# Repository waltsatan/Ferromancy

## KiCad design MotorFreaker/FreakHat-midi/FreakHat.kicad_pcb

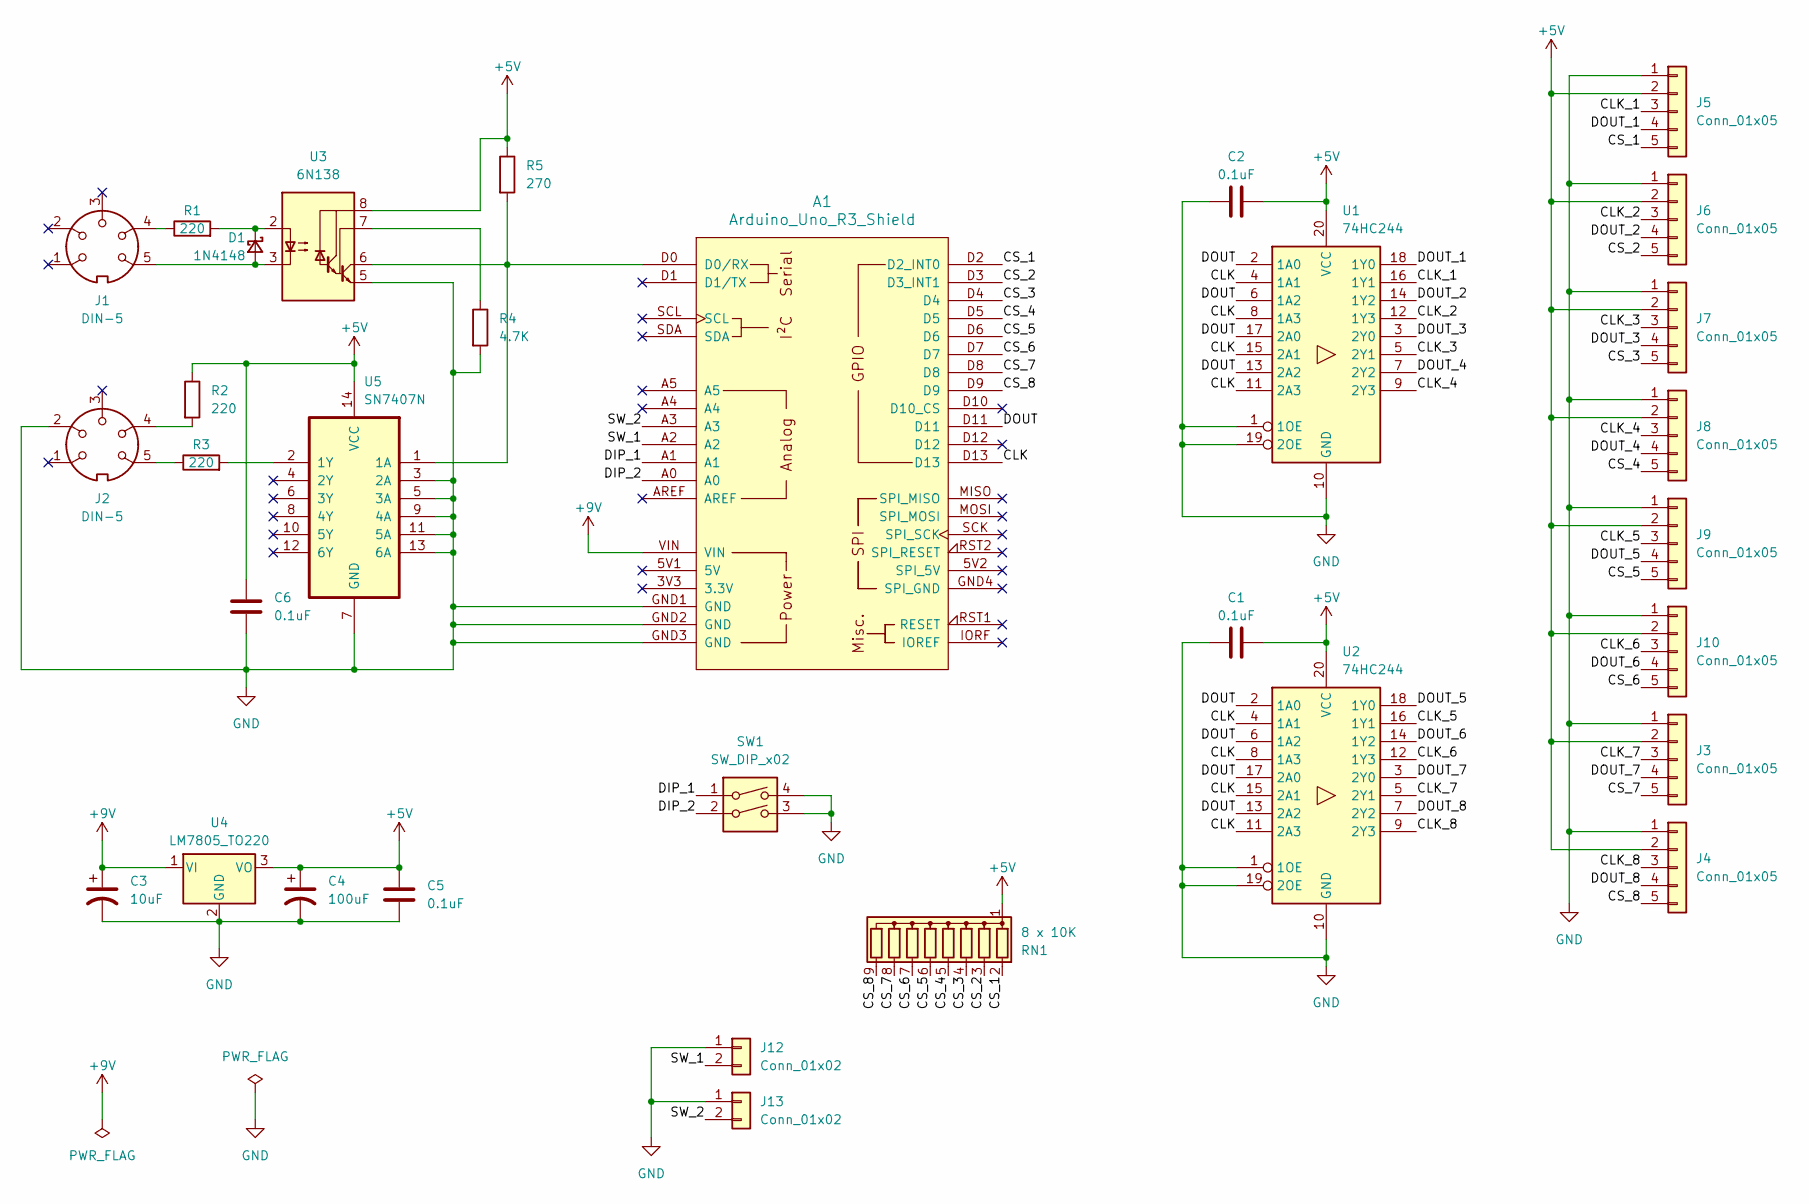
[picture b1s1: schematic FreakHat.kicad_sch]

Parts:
A1: Arduino_Uno_R3_Shield
C1, C2, C5, C6: 0.1uF; C_Disc_D3.4mm_W2.1mm_P2.50mm
C3: 10uF; CP_Radial_D5.0mm_P2.00mm
C4: 100uF; CP_Radial_D8.0mm_P3.50mm
D1: 1N4148; D_DO-35_SOD27_P7.62mm_Horizontal
J1, J2: DIN-5; DIN5_MIDI
J3, J4, J5, J6, J7, J8, J9, J10: Conn_01x05; Molex_KK-254_AE-6410-05A_1x05_P2.54mm_Vertical
J12, J13: Conn_01x02; Molex_KK-254_AE-6410-02A_1x02_P2.54mm_Vertical
R1, R2, R3: 220; R_Axial_DIN0207_L6.3mm_D2.5mm_P7.62mm_Horizontal
R4: 4.7K; R_Axial_DIN0207_L6.3mm_D2.5mm_P7.62mm_Horizontal
R5: 270; R_Axial_DIN0207_L6.3mm_D2.5mm_P7.62mm_Horizontal
RN1: 8 x 10K; R_Array_SIP9
SW1: SW_DIP_x02; SW_DIP_SPSTx02_Slide_9.78x7.26mm_W7.62mm_P2.54mm
U1, U2: 74HC244; DIP-20_W7.62mm_Socket
U3: 6N138; DIP-8_W7.62mm_Socket
U4: LM7805_TO220; TO-220-3_Vertical
U5: SN7407N; DIP-14_W7.62mm_Socket

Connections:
+5V: C1.2, C2.2, C4.1, C5.1, C6.1, J3.2, J4.2, J5.2, J6.2, J7.2, J8.2, J9.2, J10.2, R2.1, R5.1, RN1.1 (common), U1.20 (VCC), U2.20 (VCC), U3.8 (VCC), U4.3 (VO), U5.14 (VCC)
+9V: A1.VIN, C3.1, U4.1 (VI)
/CLK: A1.D13, U1.4 (1A1), U1.8 (1A3), U1.11 (2A3), U1.15 (2A1), U2.4 (1A1), U2.8 (1A3), U2.11 (2A3), U2.15 (2A1)
/CLK_1: J5.3, U1.16 (1Y1)
/CLK_2: J6.3, U1.12 (1Y3)
/CLK_3: J7.3, U1.5 (2Y1)
/CLK_4: J8.3, U1.9 (2Y3)
/CLK_5: J9.3, U2.16 (1Y1)
/CLK_6: J10.3, U2.12 (1Y3)
/CLK_7: J3.3, U2.5 (2Y1)
/CLK_8: J4.3, U2.9 (2Y3)
/CS_1: A1.D2 (D2_INT0), J5.5, RN1.2 (R1)
/CS_2: A1.D3 (D3_INT1), J6.5, RN1.3 (R2)
/CS_3: A1.D4, J7.5, RN1.4 (R3)
/CS_4: A1.D5, J8.5, RN1.5 (R4)
/CS_5: A1.D6, J9.5, RN1.6 (R5)
/CS_6: A1.D7, J10.5, RN1.7 (R6)
/CS_7: A1.D8, J3.5, RN1.8 (R7)
/CS_8: A1.D9, J4.5, RN1.9 (R8)
/DIP_1: A1.A1, SW1.1
/DIP_2: A1.A0, SW1.2
/DOUT: A1.D11, U1.2 (1A0), U1.6 (1A2), U1.13 (2A2), U1.17 (2A0), U2.2 (1A0), U2.6 (1A2), U2.13 (2A2), U2.17 (2A0)
/DOUT_1: J5.4, U1.18 (1Y0)
/DOUT_2: J6.4, U1.14 (1Y2)
/DOUT_3: J7.4, U1.3 (2Y0)
/DOUT_4: J8.4, U1.7 (2Y2)
/DOUT_5: J9.4, U2.18 (1Y0)
/DOUT_6: J10.4, U2.14 (1Y2)
/DOUT_7: J3.4, U2.3 (2Y0)
/DOUT_8: J4.4, U2.7 (2Y2)
/SW_1: A1.A2, J12.2
/SW_2: A1.A3, J13.2
GND: A1.GND1 (GND), A1.GND2 (GND), A1.GND3 (GND), C1.1, C2.1, C3.2, C4.2, C5.2, C6.2, J2.2, J3.1, J4.1, J5.1, J6.1, J7.1, J8.1, J9.1, J10.1, J12.1, J13.1, R4.2, SW1.3, SW1.4, U1.1 (1OE), U1.10 (GND), U1.19 (2OE), U2.1 (1OE), U2.10 (GND), U2.19 (2OE), U3.5 (GND), U4.2 (GND), U5.3 (2A), U5.5 (3A), U5.7 (GND), U5.9 (4A), U5.11 (5A), U5.13 (6A)
unnamed: A1.D0 (D0/RX), R5.2, U3.6 (VO2), U5.1 (1A)
unnamed: D1.2 (A), J1.5, U3.3 (C2)
unnamed: D1.1 (K), R1.2, U3.2 (C1)
unnamed: J1.4, R1.1
unnamed: J2.4, R2.2
unnamed: J2.5, R3.1
unnamed: R4.1, U3.7 (VO1)
unnamed: R3.2, U5.2 (1Y)

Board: 2 copper layers, 32 parts (0 on the bottom side), 41 nets, no tracks yet.

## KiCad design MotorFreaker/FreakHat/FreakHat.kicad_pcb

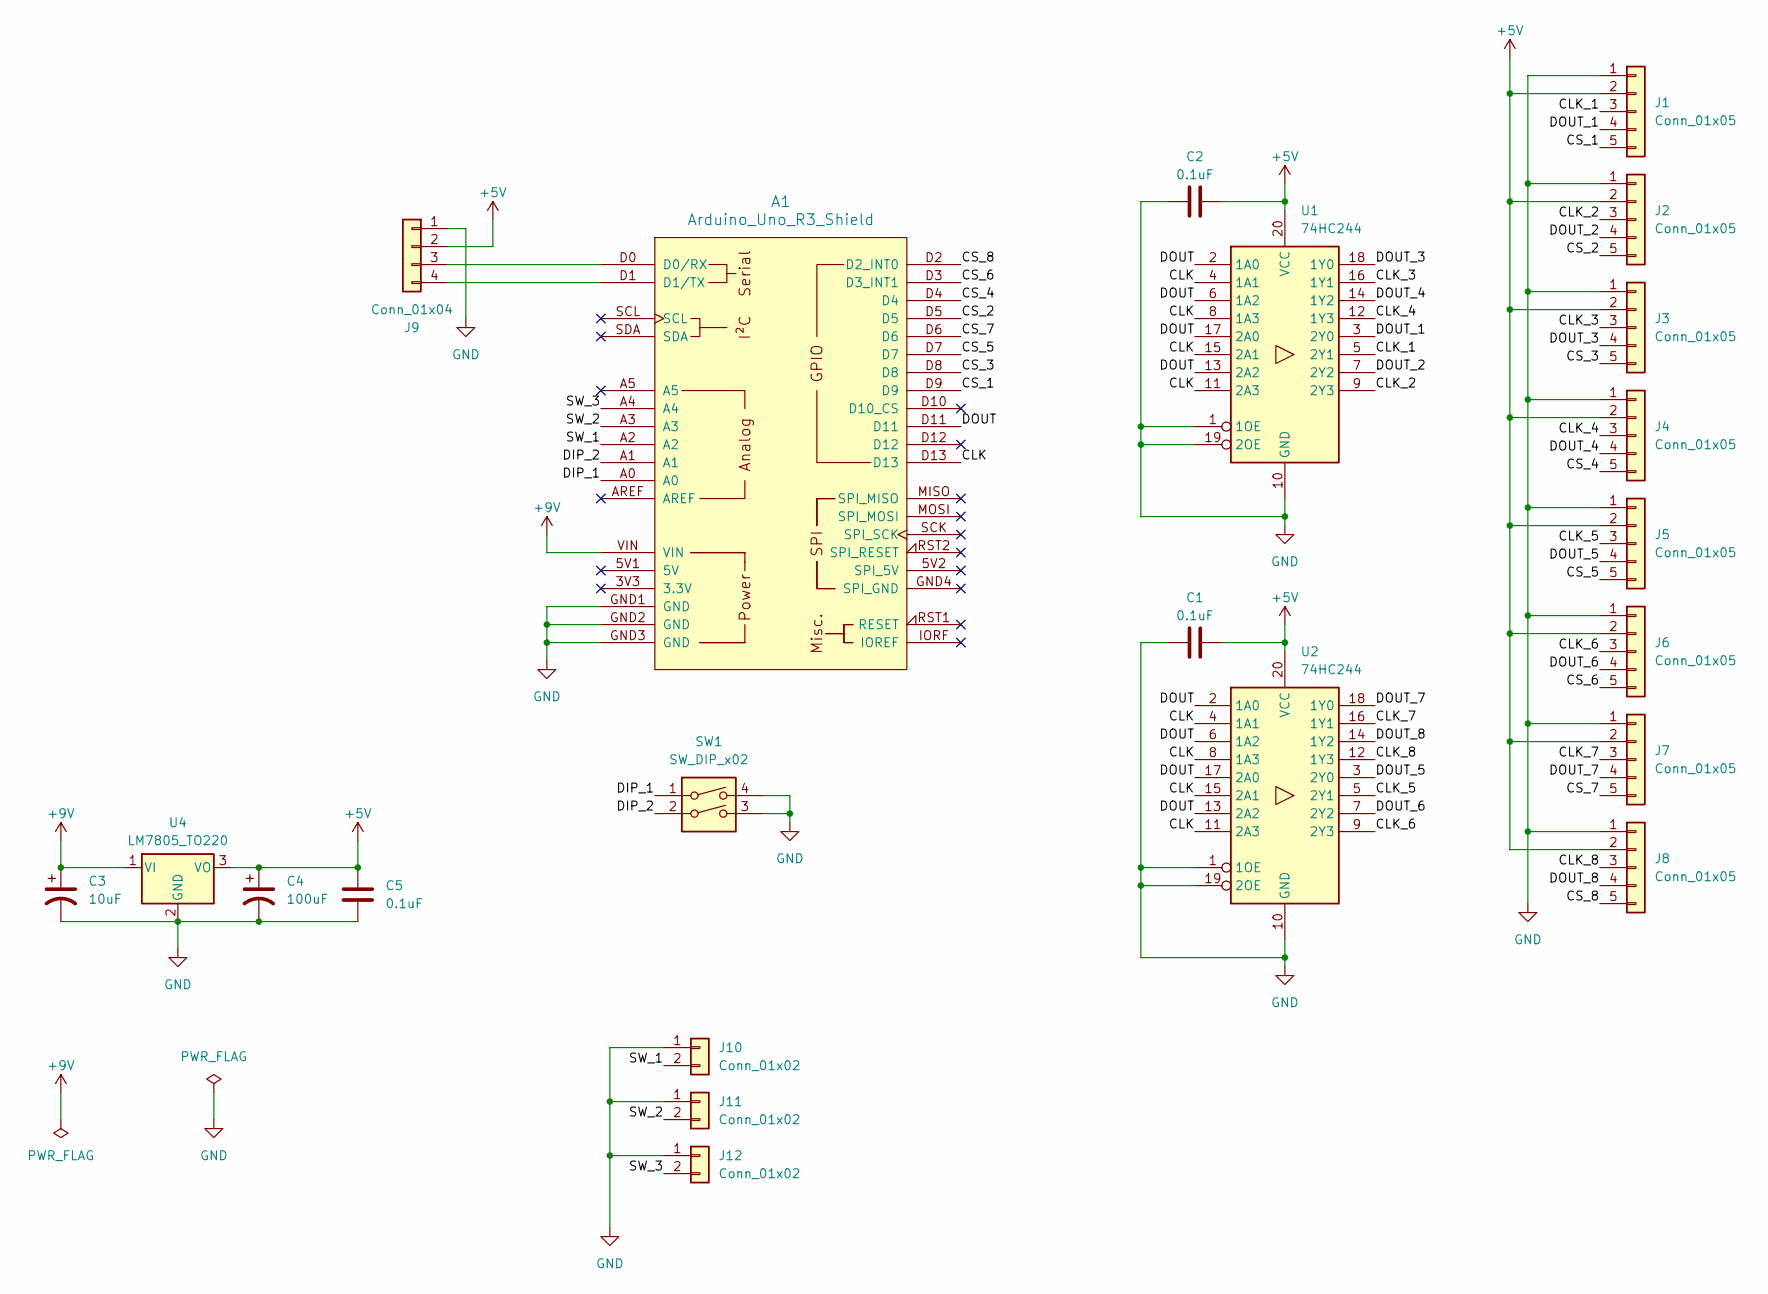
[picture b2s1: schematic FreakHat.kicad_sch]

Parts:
A1: Arduino_Uno_R3_Shield
C1, C2, C5: 0.1uF; C_Disc_D3.4mm_W2.1mm_P2.50mm
C3: 10uF; CP_Radial_D5.0mm_P2.00mm
C4: 100uF; CP_Radial_D8.0mm_P3.50mm
J1, J2, J3, J4, J5, J6, J7, J8: Conn_01x05; Molex_KK-254_AE-6410-05A_1x05_P2.54mm_Vertical
J9: Conn_01x04; Molex_KK-254_AE-6410-04A_1x04_P2.54mm_Vertical
J10, J11, J12: Conn_01x02; Molex_KK-254_AE-6410-02A_1x02_P2.54mm_Vertical
SW1: SW_DIP_x02; SW_DIP_SPSTx02_Slide_9.78x7.26mm_W7.62mm_P2.54mm
U1, U2: 74HC244; DIP-20_W7.62mm_Socket
U4: LM7805_TO220; TO-220-3_Vertical

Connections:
+5V: C1.2, C2.2, C4.1, C5.1, J1.2, J2.2, J3.2, J4.2, J5.2, J6.2, J7.2, J8.2, J9.2, U1.20 (VCC), U2.20 (VCC), U4.3 (VO)
+9V: A1.VIN, C3.1, U4.1 (VI)
/CLK: A1.D13, U1.4 (1A1), U1.8 (1A3), U1.11 (2A3), U1.15 (2A1), U2.4 (1A1), U2.8 (1A3), U2.11 (2A3), U2.15 (2A1)
/CLK_1: J1.3, U1.5 (2Y1)
/CLK_2: J2.3, U1.9 (2Y3)
/CLK_3: J3.3, U1.16 (1Y1)
/CLK_4: J4.3, U1.12 (1Y3)
/CLK_5: J5.3, U2.5 (2Y1)
/CLK_6: J6.3, U2.9 (2Y3)
/CLK_7: J7.3, U2.16 (1Y1)
/CLK_8: J8.3, U2.12 (1Y3)
/CS_1: A1.D9, J1.5
/CS_2: A1.D5, J2.5
/CS_3: A1.D8, J3.5
/CS_4: A1.D4, J4.5
/CS_5: A1.D7, J5.5
/CS_6: A1.D3 (D3_INT1), J6.5
/CS_7: A1.D6, J7.5
/CS_8: A1.D2 (D2_INT0), J8.5
/DIP_1: A1.A0, SW1.1
/DIP_2: A1.A1, SW1.2
/DOUT: A1.D11, U1.2 (1A0), U1.6 (1A2), U1.13 (2A2), U1.17 (2A0), U2.2 (1A0), U2.6 (1A2), U2.13 (2A2), U2.17 (2A0)
/DOUT_1: J1.4, U1.3 (2Y0)
/DOUT_2: J2.4, U1.7 (2Y2)
/DOUT_3: J3.4, U1.18 (1Y0)
/DOUT_4: J4.4, U1.14 (1Y2)
/DOUT_5: J5.4, U2.3 (2Y0)
/DOUT_6: J6.4, U2.7 (2Y2)
/DOUT_7: J7.4, U2.18 (1Y0)
/DOUT_8: J8.4, U2.14 (1Y2)
/SW_1: A1.A2, J10.2
/SW_2: A1.A3, J11.2
/SW_3: A1.A4, J12.2
GND: A1.GND1 (GND), A1.GND2 (GND), A1.GND3 (GND), C1.1, C2.1, C3.2, C4.2, C5.2, J1.1, J2.1, J3.1, J4.1, J5.1, J6.1, J7.1, J8.1, J9.1, J10.1, J11.1, J12.1, SW1.3, SW1.4, U1.1 (1OE), U1.10 (GND), U1.19 (2OE), U2.1 (1OE), U2.10 (GND), U2.19 (2OE), U4.2 (GND)
unnamed: A1.D0 (D0/RX), J9.3
unnamed: A1.D1 (D1/TX), J9.4

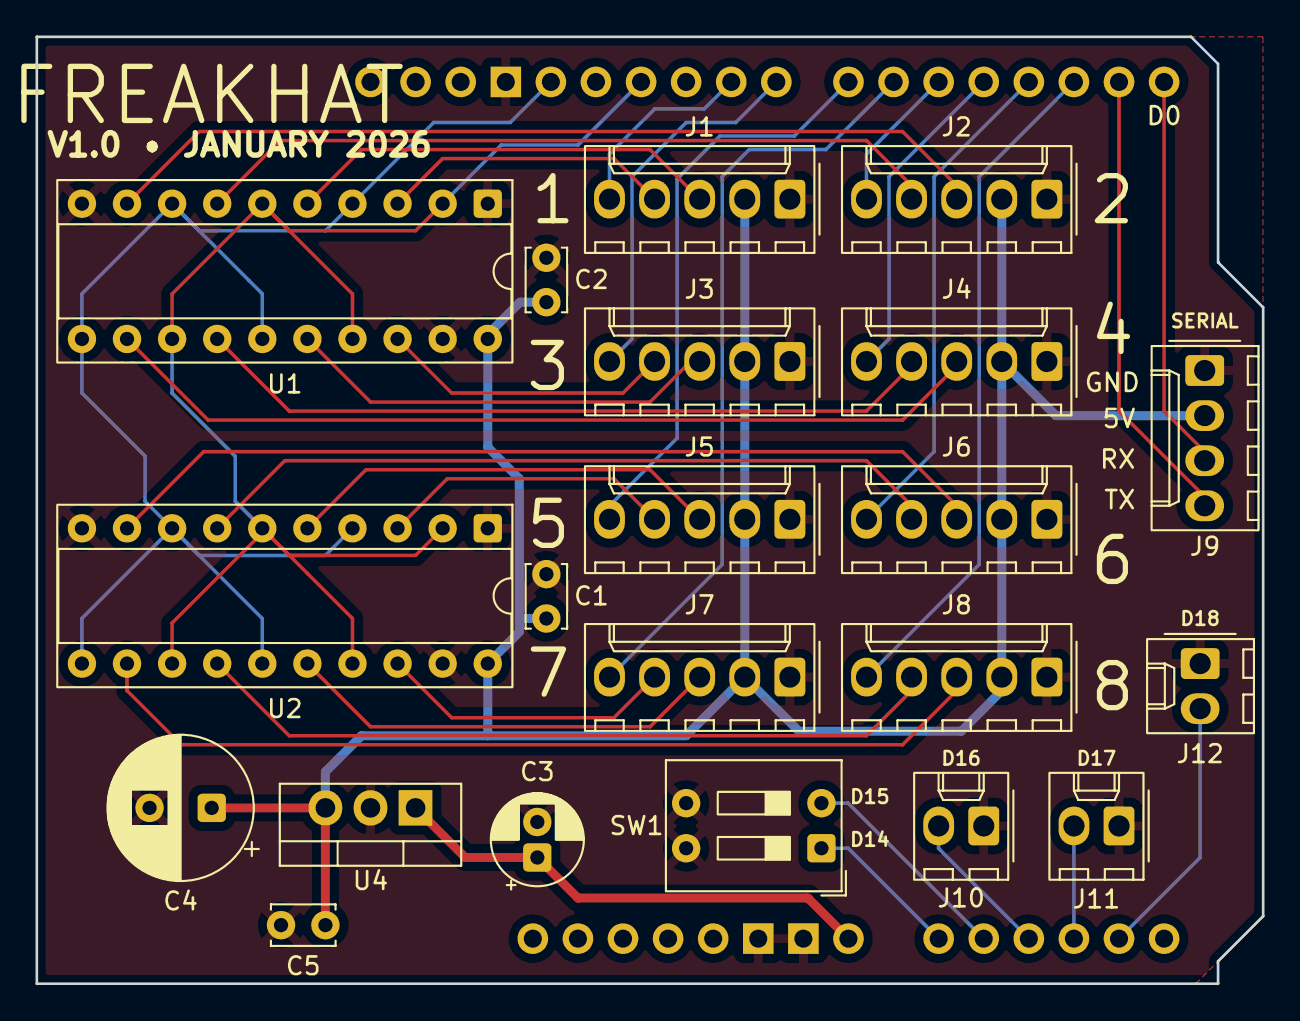
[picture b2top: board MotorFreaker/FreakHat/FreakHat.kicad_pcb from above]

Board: 2 copper layers, 69.1 x 53.3 mm, 22 parts (0 on the bottom side), 36 nets.

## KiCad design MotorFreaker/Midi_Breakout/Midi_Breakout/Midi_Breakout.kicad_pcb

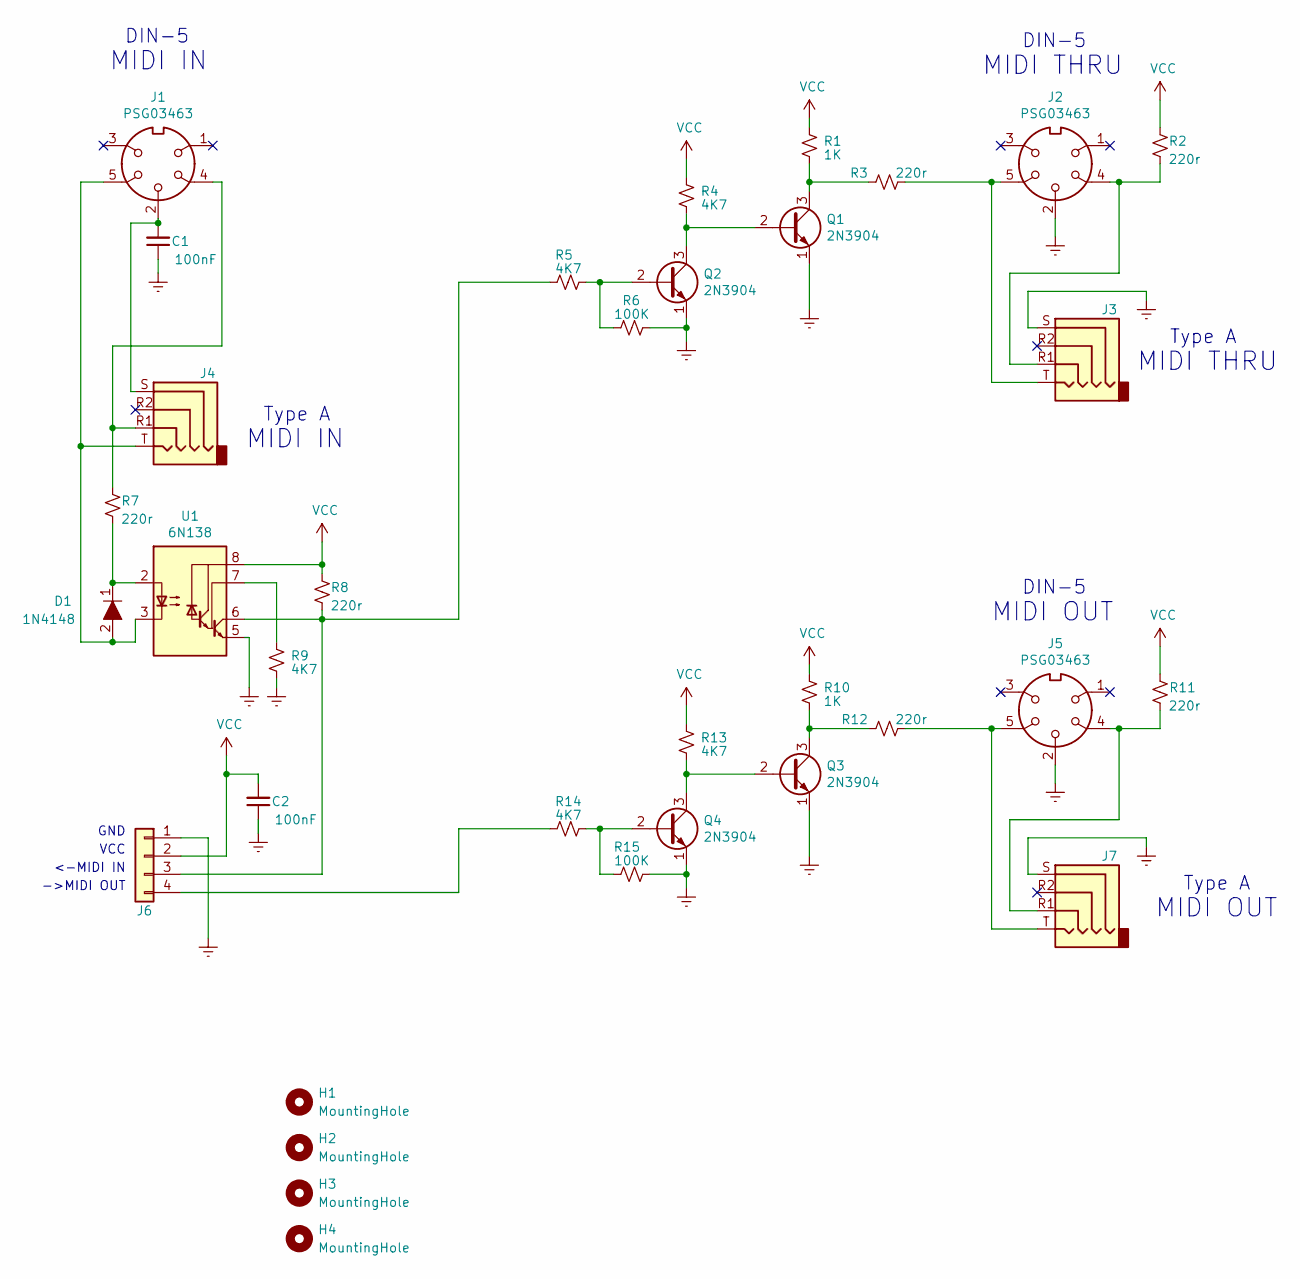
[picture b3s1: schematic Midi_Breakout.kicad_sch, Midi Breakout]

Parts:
C1, C2: 100nF; C_Disc_D3.8mm_W2.6mm_P2.50mm
D1: 1N4148; D_DO-35_SOD27_P10.16mm_Horizontal; MPN 1N4148; Digi-Key_PN 1N4148FS-ND
H1, H2, H3, H4: MountingHole; MountingHole_3.5mm
J1, J2, J5: PSG03463; DIN5
J3, J4, J7: AudioJack4; PJ320A
J6: Conn_01x04; Molex_KK-254_AE-6410-04A_1x04_P2.54mm_Vertical
Q1, Q2, Q3, Q4: 2N3904; TO-92_Inline_Wide
R1, R10: 1K; R_Axial_DIN0207_L6.3mm_D2.5mm_P10.16mm_Horizontal
R2, R3, R7, R8, R11, R12: 220r; R_Axial_DIN0207_L6.3mm_D2.5mm_P10.16mm_Horizontal
R4, R5, R9, R13, R14: 4K7; R_Axial_DIN0207_L6.3mm_D2.5mm_P10.16mm_Horizontal
R6, R15: 100K; R_Axial_DIN0207_L6.3mm_D2.5mm_P10.16mm_Horizontal
U1: 6N138; DIP-8_W7.62mm_Socket

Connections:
GNDREF: C1.1, C2.1, J2.2, J3.S, J5.2, J6.1, J7.S, Q1.1 (E), Q2.1 (E), Q3.1 (E), Q4.1 (E), R6.1, R9.1, R15.1, U1.5 (GND)
unnamed: C1.2, J1.2, J4.S
unnamed: J1.4, J4.R1, R7.1
unnamed: J2.4, J3.R1, R2.2
unnamed: J2.5, J3.T, R3.1
unnamed: J5.4, J7.R1, R11.2
unnamed: J5.5, J7.T, R12.1
unnamed: J6.3, R5.1, R8.2, U1.6 (VO2)
unnamed: J6.4, R14.1
unnamed: Q1.2 (B), Q2.3 (C), R4.1
unnamed: Q1.3 (C), R1.1, R3.2
unnamed: Q2.2 (B), R5.2, R6.2
unnamed: Q3.2 (B), Q4.3 (C), R13.1
unnamed: Q3.3 (C), R10.1, R12.2
unnamed: Q4.2 (B), R14.2, R15.2
unnamed: D1.1, R7.2, U1.2 (C1)
unnamed: D1.2, J1.5, J4.T, U1.3 (C2)
unnamed: R9.2, U1.7 (VO1)
VCC: C2.2, J6.2, R1.2, R2.1, R4.2, R8.1, R10.2, R11.1, R13.2, U1.8 (VCC)

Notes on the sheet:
->MIDI OUT
MIDI THRU
MIDI OUT
GND
DIN-5
Type A
VCC
<-MIDI IN
MIDI IN

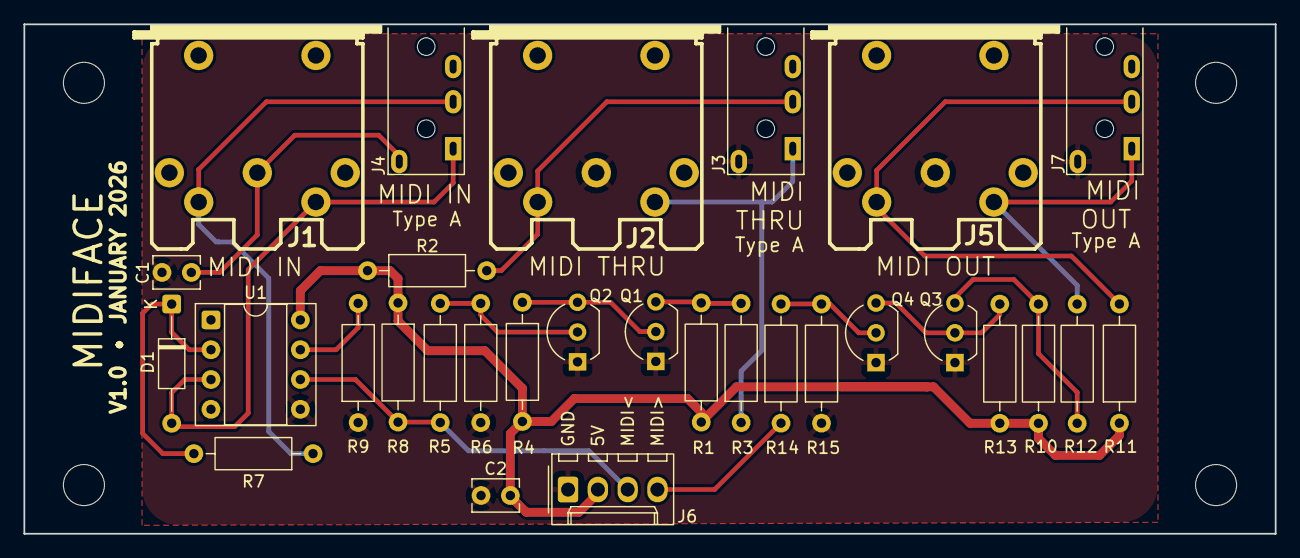
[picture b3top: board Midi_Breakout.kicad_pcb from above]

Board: 2 copper layers, 106.7 x 43.4 mm, 34 parts (0 on the bottom side), 19 nets.

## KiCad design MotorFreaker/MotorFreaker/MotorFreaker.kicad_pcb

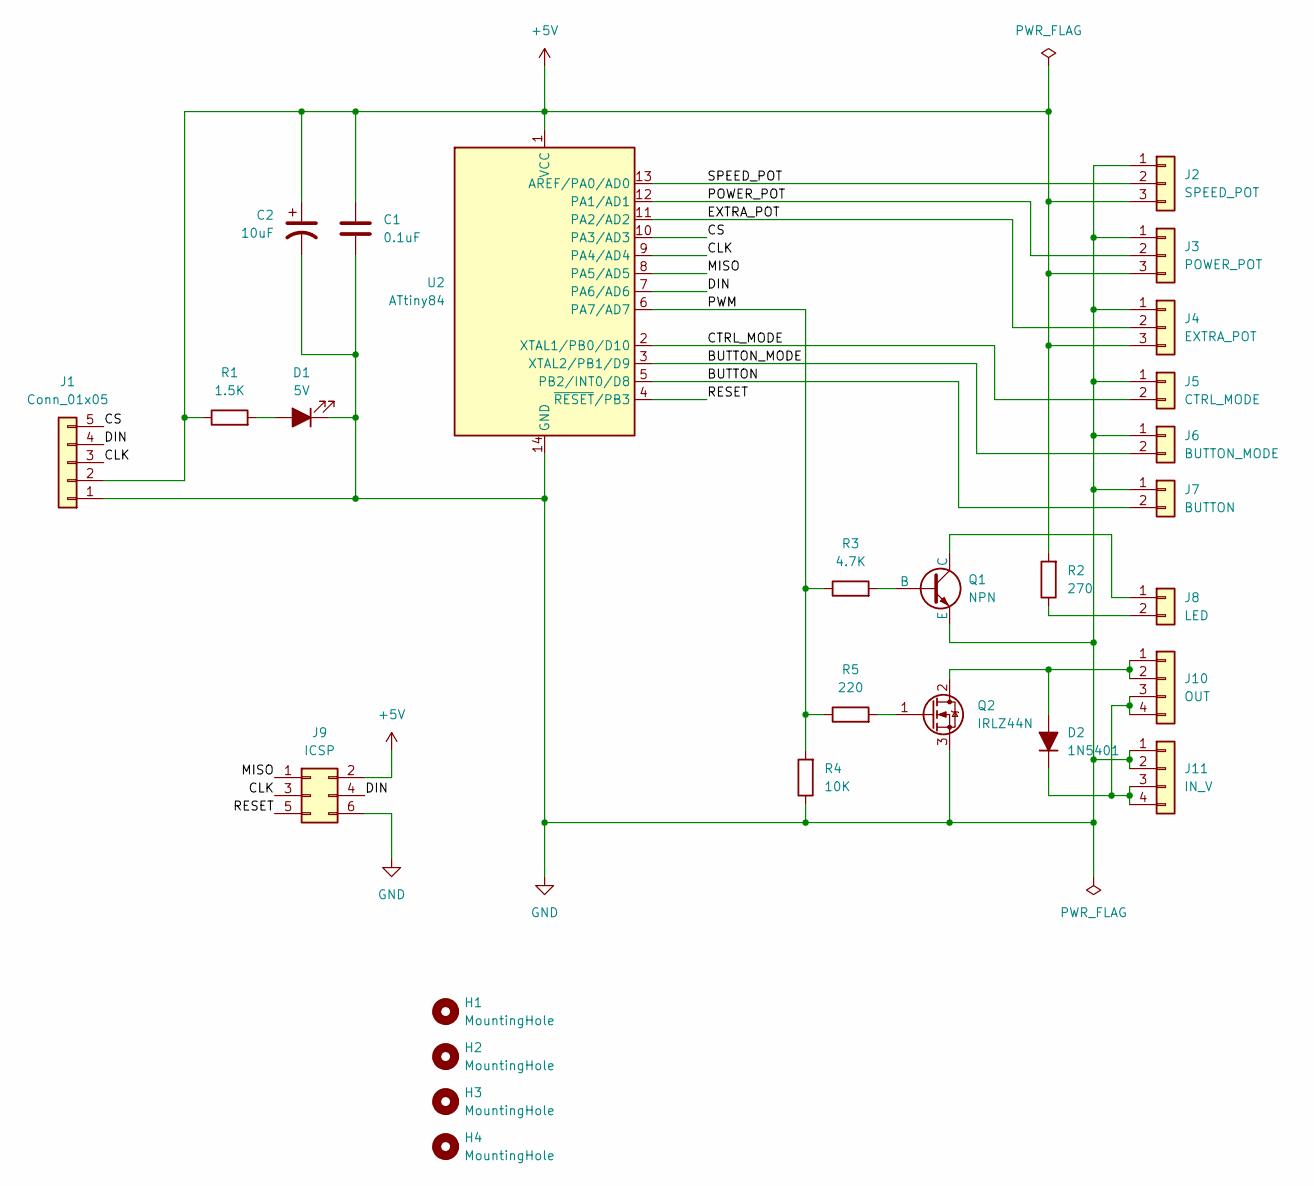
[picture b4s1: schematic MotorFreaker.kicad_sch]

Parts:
C1: 0.1uF; C_Disc_D3.4mm_W2.1mm_P2.50mm
C2: 10uF; CP_Radial_D5.0mm_P2.00mm
D1: 5V; LED_D3.0mm
D2: 1N5401; D_DO-201AD_P12.70mm_Horizontal
H1, H2, H3, H4: MountingHole; MountingHole_3.5mm
J1: Conn_01x05; Molex_KK-254_AE-6410-05A_1x05_P2.54mm_Vertical
J2: SPEED_POT; Molex_KK-254_AE-6410-03A_1x03_P2.54mm_Vertical
J3: POWER_POT; Molex_KK-254_AE-6410-03A_1x03_P2.54mm_Vertical
J4: EXTRA_POT; Molex_KK-254_AE-6410-03A_1x03_P2.54mm_Vertical
J5: CTRL_MODE; Molex_KK-254_AE-6410-02A_1x02_P2.54mm_Vertical
J6: BUTTON_MODE; Molex_KK-254_AE-6410-02A_1x02_P2.54mm_Vertical
J7: BUTTON; Molex_KK-254_AE-6410-02A_1x02_P2.54mm_Vertical
J8: LED; Molex_KK-254_AE-6410-02A_1x02_P2.54mm_Vertical
J9: ICSP; PinHeader_2x03_P2.54mm_Vertical
J10: OUT; QT02ADP83H0000G
J11: IN_V; QT02ADP83H0000G
Q1: NPN; TO-92L_Inline_Wide
Q2: IRLZ44N; TO-220-3_Vertical
R1: 1.5K; R_Axial_DIN0207_L6.3mm_D2.5mm_P7.62mm_Horizontal
R2: 270; R_Axial_DIN0207_L6.3mm_D2.5mm_P7.62mm_Horizontal
R3: 4.7K; R_Axial_DIN0207_L6.3mm_D2.5mm_P7.62mm_Horizontal
R4: 10K; R_Axial_DIN0207_L6.3mm_D2.5mm_P7.62mm_Horizontal
R5: 220; R_Axial_DIN0207_L6.3mm_D2.5mm_P7.62mm_Horizontal
U2: ATtiny84; DIP-14_W7.62mm

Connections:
+5V: C1.1, C2.1, J1.2, J2.3, J3.3, J4.3, J9.2, R1.1, R2.2, U2.1 (VCC)
/BUTTON: J7.2, U2.5 (PB2/INT0/D8)
/BUTTON_MODE: J6.2, U2.3 (XTAL2/PB1/D9)
/CLK: J1.3, J9.3, U2.9 (PA4/AD4)
/CS: J1.5, U2.10 (PA3/AD3)
/CTRL_MODE: J5.2, U2.2 (XTAL1/PB0/D10)
/DIN: J1.4, J9.4, U2.7 (PA6/AD6)
/EXTRA_POT: J4.2, U2.11 (PA2/AD2)
/MISO: J9.1, U2.8 (PA5/AD5)
/POWER_POT: J3.2, U2.12 (PA1/AD1)
/PWM: R3.1, R4.2, R5.1, U2.6 (PA7/AD7)
/RESET: J9.5, U2.4 (~RESET/PB3)
/SPEED_POT: J2.2, U2.13 (AREF/PA0/AD0)
GND: C1.2, C2.2, D1.1 (K), J1.1, J2.1, J3.1, J4.1, J5.1, J6.1, J7.1, J9.6, J11.1, J11.2, Q1.3 (E), Q2.3 (S), R4.1, U2.14 (GND)
unnamed: D1.2 (A), R1.2
unnamed: D2.2 (A), J10.1, J10.2, Q2.2 (D)
unnamed: D2.1 (K), J10.3, J10.4, J11.3, J11.4
unnamed: J8.1, Q1.1 (C)
unnamed: J8.2, R2.1
unnamed: Q1.2 (B), R3.2
unnamed: Q2.1 (G), R5.2

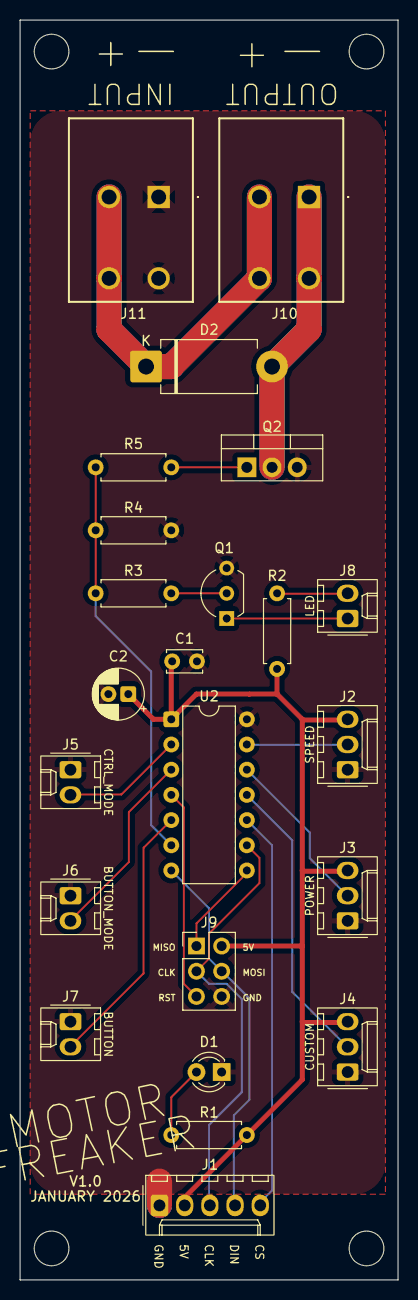
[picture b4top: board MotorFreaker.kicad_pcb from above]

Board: 2 copper layers, 38.1 x 127.0 mm, 27 parts (0 on the bottom side), 21 nets.

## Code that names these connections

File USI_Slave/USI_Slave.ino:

/*  USI SPI Slave Demo written by Robert Mollik, 2016
 *  
 *  This demo uses the SPI protocol with USI interface. This is necessary with with the smaller AVR controller since they don't 
 *  a complete SPI functionality. 
 *  Demo is written for the pinout of an Arduino Trinket and ATtiny85. Pins need to be modified if a different controller is used.
 *  
 *  The demo takes receives a request ID from the Master at the beginning of every communication. According to the request ID,
 *  it sends back either a temperature or a humidity values. Since both values are present in float, the 4 bytes of the float need
 *  to be send separately.
 */

#define CSp    PA3//PA0 //PB3     // Chip select
#define LED   PA7 //PB4     // Test LED
#define DO    PA5     // MISO or Data Out
#define USCK  PA4     // Clock
#include <wiring_private.h>
// Variable use in Interrupt need to be volotile to tell the compiler, they may be altered in other functions than in Main loop.
// Otherwise the compiler could remove or replace them with a constant:

volatile char reqID = 0;              // This is for the first byte we receive, which is intended to be the request identifier
volatile uint8_t index = 0;           // this is to send back the right element in the array
volatile char ana = 0;  
// Test variables:

volatile byte temperature = 10;
volatile byte humidity = 20;

// Pointer on the test variables. Datatype is casted into byte to read out the single bytes of the float:

byte * tempPTR = (byte*) &temperature;
byte * humPTR  = (byte*) &humidity;

void setup (void)
{
  cli();                              // Deactivate Interrupts
 // pinMode(LED, OUTPUT);
  DDRA |= 1<<LED;                     // Set PB1 as output (LED on Trinket) / PB0 will be the Input for the Interrupt
  DDRA |= 1<<DO;                      // MISO Pin has to be an output

  USICR = ((1<<USIWM0)|(1<<USICS1));  // Activate 3- Wire Mode and use of external clock but NOT the interrupt at the Counter overflow (USIOIE)
  
  PORTA |= 1<<LED;                    // Turn PB1 off
  PORTA |= 1<<CSp;                     // Activate Pull-Up resistor on PB0
  
   GIMSK = (1 << PCIE0);
    PCMSK0 = (1 << CSp);
sei();

 delay(200);
  digitalWrite(7, HIGH);
   delay(500);
   digitalWrite(7, LOW);
   delay(500);
  digitalWrite(7, HIGH);
   delay(500);
  digitalWrite(7, LOW);
   delay(500);
      
 // PORTA^= 1<<LED;    
  //PORTA= 1<<LED;
  //pinMode(7,OUTPUT);    
  //analogWrite(7,150);    
   sei();                  
}  // end of setup


// Interrupt routine at the CS pin. Always executed when value on CS pin changes:

ISR(PCINT0_vect)
  {    
    //PORTA= 0<<LED;  
    if((PINA & (1<<CSp))== 0){
      
      // If edge is falling, the command and index variables shall be initialized
      // and the 4-bit overflow counter of the USI communication shall be activated:

      reqID = 0;
      index = 0;
      USICR |= (1<<USIOIE);
      USISR = 1<<USIOIF;      // Clear Overflow bit

      // XOR operation to turn PB3 (LED) on/off. (Not needed for USI)
      
      //PORTA^= 1<<LED;  
    } else{

      // If edge is rising, turn the 4-bit overflow interrupt off:
      
      USICR &= ~(1<<USIOIE);
    }
  }

 // USI interrupt routine. Always executed when 4-bit overflows (after 16 clock edges = 8 clock cycles):

ISR(USI_OVF_vect)
  {  
    
      switch(reqID){

        // Switch-Case to respond according to request from Master:

        case 0:               // If reqID value is zero (just initialized), then first message is the reqID.
          temperature++; 
          //PORTA^= 1<<LED; 
          reqID = USIDR;      // Read in from USIDR register
          USISR = 1<<USIOIF;  // Clear Overflow bit
          break;
        case 'L': {
            ana = USIDR;      // Read in from USIDR register
            // analogWrite(7,ana);
            sbi(TCCR0A, COM0B1); 
            OCR0B = ana; 
            //PORTA= 0<<LED;  
            USISR = 1<<USIOIF;  // Clear Overflow bit
            reqID=0;
            break;

        }
        
        case 'T':

          // Write value to send back into USIDR and clear the overflow bit:
          USIDR = temperature;//tempPTR[index];
          USISR = 1<<USIOIF;      
           
          index++;            // Increment index to transmit the folloing element next
          break;
          
        case 'H':
        
          // Write value to send back into USIDR and clear the overflow bit:
          USIDR = humidity;//humPTR[index]; 
          USISR = 1<<USIOIF; 
          //humidity++;
          index++;            // Increment index to transmit the folloing element next
          break;

        default:
          // Default option of Switch-Case. Send 'reqID' back for debugging.
          USIDR = reqID;
          USISR = 1<<USIOIF;
          
      }      
  }

void loop (void)
{
  // Nothing done here in this example
}  

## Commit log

2026-01-11 init
2026-01-12 sliders
2026-01-16 fins
2026-01-21 module
2026-01-23 freaker
2026-01-25 layout
2026-01-26 midi
